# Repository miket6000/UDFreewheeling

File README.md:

# UDFreewheeling
A Freewheeling DRSSTC controller based loosely on the UD2.7. See it running my 35cm coil here: (https://youtu.be/EUlrq9CbajI)

Follow the development history at https://highvoltageforum.net/index.php?topic=2054.0

The driver behind building a new Tesla Coil Controller was to create something as simple to build and use as the UD2.7 (https://loneoceans.com/labs/ud27/) but with the below improvements:
* Freewheeling over current protection, this limits the maximum current without terminating the burst
* Over current and current phase detected with a single current transformer (CT)
* Removed the need for difficult to obtain variable inductors
* Self oscillating for improved startup at lower feedback currents

There are a couple of breaking changes that are worth pointing out:
* While the board outline is approximately the same as UD2.7 I can't guarantee the mounting holes are in the exact same locations
* There is no longer the ability to disable phase lead, it wasn't obvious why this would be required and can be done by using a short instead of L1
* The location of the HFBR is approximately the same as the UD2.7 but the location of the IF-D95 has changed slightly

Huge thanks to the assistance of all those at highvoltageforum.net and especially David Knierim for his extensive contributions.

## How it works
### Power supply
There's nothing much here to talk about, there are three regulators, 24V, 9V and 5V. 24V and 5V are linear, the 9V should be a DC/DC converter such as  RECOM Power R-78E9.0-0.5 or similar. It is recommended for the input supply that you use a 1A 24V SMPS and the DC input. Do not use the DC and AC inputs at the same time.

### Phase detect
The CT should be designed to provide a current of ~500mA to 1A peak at maximum primary current.
C32 provides HF bypass for noise. The current from the CT passes through R3 || R8 L1 and R1 generating a voltage ton pin 1 of R8 hat leads the current by theta = arctan(Xl / R). Xl depends on the operating frequency of the primary but R just depends on the position of the wiper on R8 and can be set from 5.1R up to R3 || R9 which is approximately 22R. This voltage is then clamped to +/- 0.65V by the back to back diodes and capacitvely coupled into the inverting input of the comparator IC8.

IC8 is set up with both positive and negative feedback with the non-inverting input held at nominally 2.5V. If we initially ignore any input from the CT we can see that the comparator will attempt to pull the inverting input low. There will be a time constant set by C5 and (R21 + R25) which will mean this takes some amount of time but the voltage at the input will be reducing. Meanwhile when the input transitioned low C33, R26 and R7 immediately pulled the non-inverting input low but C33 will slowly charge so the voltage at the non-inverting input will be increasing.

After some amount of time the increasing voltage on the non-inverting input and the decreasing voltage in the inverting input will be equal and the pass each other. At this moment the comparator will toggle states at the output will go high. This will reverse our initial state and everything happens again, but with the voltages reversed, i.e. it oscillates. The oscillation frequency can be set by adjusting R25. This should be set as close as possible to the frequency of the primary. To set the correct frequency ensure there is no feedback from the CT (i.e. disconnect the output stage or the CT) and measure the frequency on an oscilloscope. Adjust R25 until this matches your expected resonant frequency.

When there is a signal from the CT it swamps the ability of the negative feedback from R21 + R25 to control the inverting input pin so is effectively overriden with the natural resonant frequency of the system.

### Over current detection
The current through the CT creates a voltage across R1 (5R1). This is clamped between the 0V and 5V rails and feed into the inverting input of U5A. If the voltage exceeds the voltage set by R20 then the output of the comparator will go low signaling an over current event to the logic controlling the gate drivers. The over current threshold is determined by taking your intended over current peak, dividing it by the CT ratio and multiplying by 5.1V. R20 is then adjusted until this voltage is measured on TP6. E.G. I have a 300:1 CT and want the over current limit to be set to 200A, so I adjust R20 until I see 200A / 300 * 5.1V = 3.4V.

### Interrupt input
A signal present on the optical input of RX1 (active low) is inverted by IC4F so that the output is high when the signal is present (LED on). A signal present on the optical input of RX2 (active high) is first inverted and the pulls down the same node as RX1 which is then inverted again so that the output is again high when the signal is present. The two RX inputs are effectively OR'd together so it is not recommended to use both inputs at the same time. If RX2 is not placed it is necessary to either tie the input of IC4B low (by shorting RX2-RX1) or remove D12. Note, if you do decide to remove D12 it is still necessary to include R11 to prevent oscillation caused by a floating input to IC4B.

### Undervoltage Lockout (UVLO)
The under voltage lockout compares the 24V rail (divided by 6 and applied to the non-inverting input of U5B) to the reference voltage set by R27 applied to the inverting input of U5B. If the voltage drops below the reference voltage the output goes low signaling to the gate drive logic that an undervoltage has occured. The reference is set by dividing your desired UVLO voltage by 6 and adjusting R27 until you see the desired voltage on TP4. E.G. I want UVLO to trigger at 18V, 18V / 6 = 3V so I adjust R27 until I measure 3V on TP4.

### Gate drivers
This is borrowed directly from UD2.7C, the two UCC27423 dual inverting gate drivers are used to drive two FDD8424H complementry MOSFETs to run the gate drive transformers. The only difference is that there are seperate signals for the two GDTs. This means it is not possible to parallel the twou outputs, each needs to run its own GDT, one for each half of the full bridge. 

### Gate drive logic
This is the complex part. We'll start at the gate drivers and move backwards...
IC12 is a multiplexer. It has two sets of 4 inputs and will take one of the two sets of inputs and connect them to the outputs. The schematic uses a slightly different nomenclature than the datasheet but for each pair of input pins ('I0a' & 'I1a' are one pair) if the 'S' pin is low then the voltage at input 'I0a' is connected to output 'Za', if the 'S' pin is high then the voltage at 'I1a' is connected to 'Za'. All the pairs are switched at the same time. This is all assuming the Enable (E) pin is low, otherwise the outputs are all low.

We connect CLK to our 'S' pin. Looking at the 'a' and 'b' inputs which connect to GDT1 we can see that 'Za' and 'Zb' have complementy outputs, if 'Za' is high, 'Zb' is low and vice-verse. CLK is derived from our phase signal so always drives GDT1 in phase with the phase signal. Inputs 'c' and 'd' are more complex. They are driven by the putpus of IC6B so depending on the state of IC6B could be either driven in phase or out of phase with CLK. If they're driven in phase with CLK (i.e. 'Q' is high) then both sides of the H-bridge will be in phase with each other and there will be no voltage across the primary tank circuit, i.e. we're freewheeling. The currents in the LC circuit are free to slosh backwards and forwards without significant resistance from the bridge. If however 'Q' is low then the output to GDT2 is out of phase and the HVDC bus voltage will occure across the primary tank causing it to ring up.

IC6B samples IC6A's 'Qn' output and latches it for the next clock cycle on every rising 'CLK' edge. Under "normal" circumstances IC6A clocks in 5V on the 'D' pin so 'Qn' is 0V. 0V on the 'D' pin of IC6B means the drive is out of phase and we ring up the current. If however OCD is asserted low by the over current detect comparator at any stage during the clock cycle the output of IC6B's 'Qn' output will go high. It will stay high until the next clock edge samples the 'D' input and drives 'Qn' low again, but going low takes time, before that happens the state has already been samples by IC6B and locked in for the next cycle. The INTERRUPT signal on the 'set' pin just ensures that we're in the correct state (freewheeling off) in between on signals from the interrupter, otherwise we wouldn't be able to start.

IC5A will disable the output of IC12 whenever INTERRUPT is low and there is a rising edge on the CLK signal. It can also disable IC12 if its 'R' line is asserted low by IC5B which is used to latch the UVLO signal. This means that if the UVLO is triggered then the output will remain locked out until the next rising edge of INTERRUPT.

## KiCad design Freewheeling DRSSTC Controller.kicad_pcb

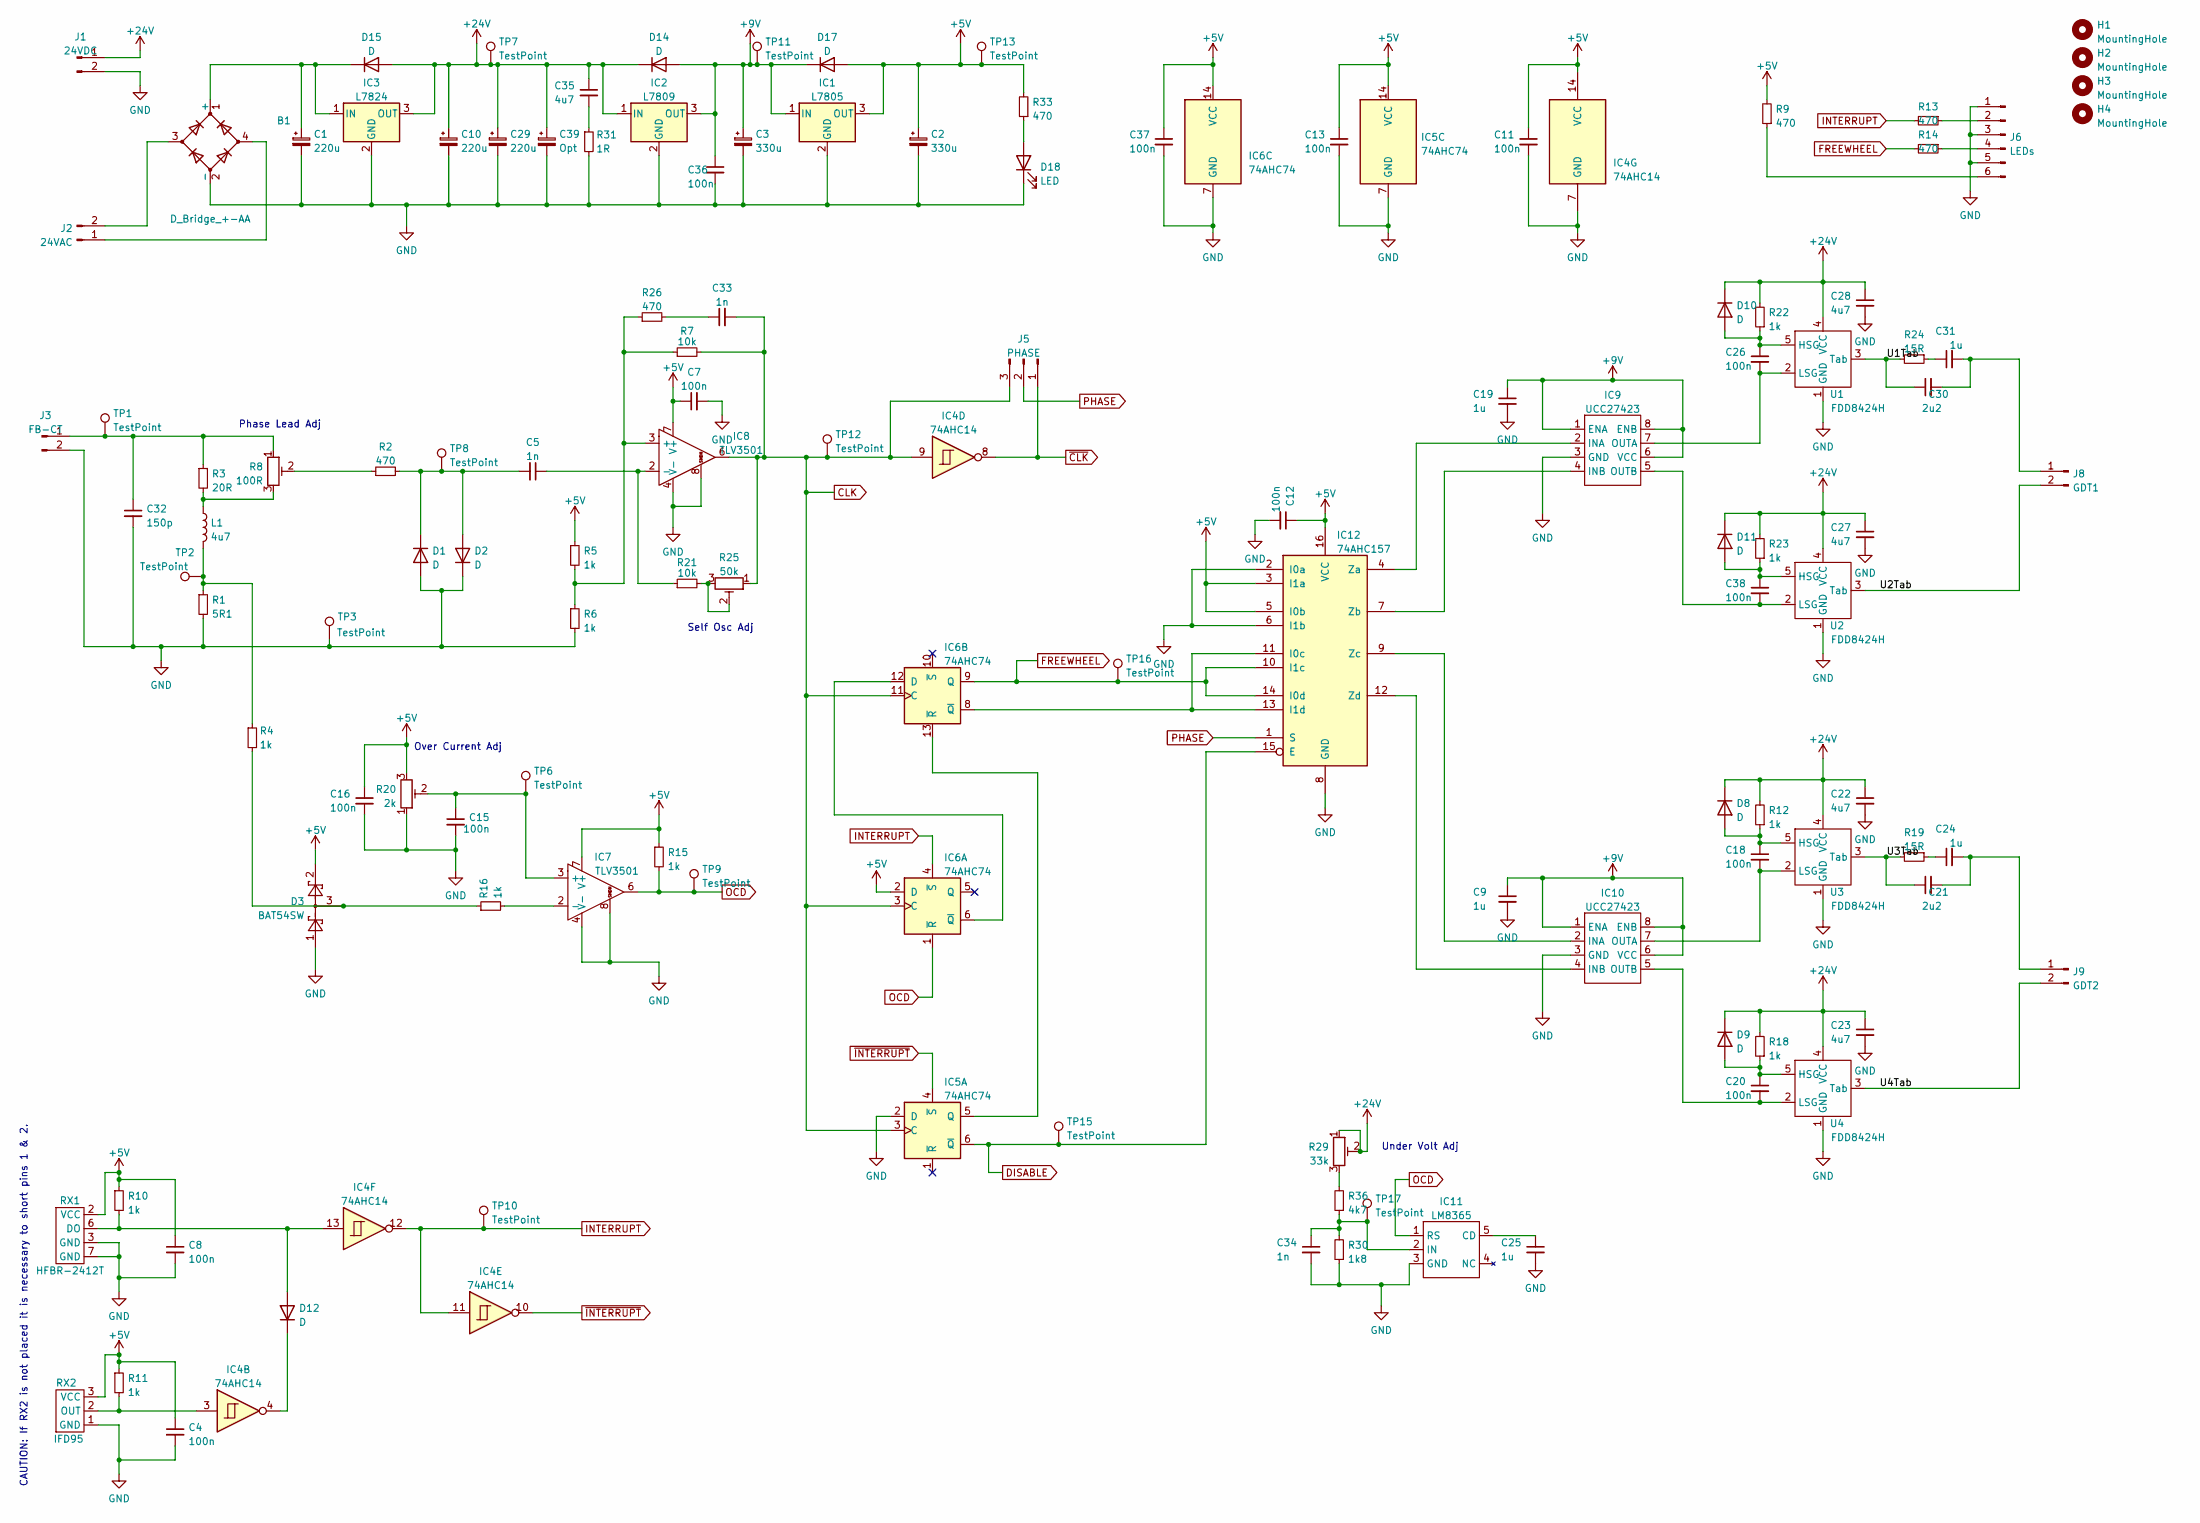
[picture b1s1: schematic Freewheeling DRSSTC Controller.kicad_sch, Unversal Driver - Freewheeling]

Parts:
B1: D_Bridge_+-AA; Diode_Bridge_Vishay_DFS
C1, C10, C29: 220u; CP_Radial_D8.0mm_P3.50mm
C2, C3: 330u; CP_Radial_D8.0mm_P3.50mm
C4, C7, C8, C11, C12, C13, C15, C16, C18, C20, C26, C36, C37, C38: 100n; C_0805_2012Metric
C5, C33, C34: 1n; C_0805_2012Metric
C9, C19, C25: 1u; C_0805_2012Metric
C21, C30: 2u2; C_1210_3225Metric
C22, C23, C27, C28, C35: 4u7; C_1206_3216Metric
C24, C31: 1u; C_1206_3216Metric
C32: 150p; C_0805_2012Metric
C39: Opt; CP_Radial_D8.0mm_P3.50mm
D1, D2, D14, D15, D17: D; D_SOD-123
D3: BAT54SW; SOT-23
D8, D9, D10, D11, D12: D; D_SOD-323
D18: LED; D_0805_2012Metric
H1, H2, H3, H4: MountingHole; MountingHole_3.2mm_M3
IC1: L7805; TO-252-3_TabPin2
IC2: L7809; TO-220-3_Vertical
IC3: L7824; TO-263-2
IC4: 74AHC14; SOIC-14_3.9x8.7mm_P1.27mm
IC5, IC6: 74AHC74; SOIC-14_3.9x8.7mm_P1.27mm
IC7, IC8: TLV3501; SOIC-8_3.9x4.9mm_P1.27mm
IC9, IC10: UCC27423; SOIC-8_3.9x4.9mm_P1.27mm
IC11: LM8365; SOT-23-5
IC12: 74AHC157; SOIC-16_3.9x9.9mm_P1.27mm
J1: 24VDC; JST_XH_B2B-XH-A_1x02_P2.50mm_Vertical
J2: 24VAC; JST_XH_B2B-XH-A_1x02_P2.50mm_Vertical
J3: FB-CT; JST_XH_B2B-XH-A_1x02_P2.50mm_Vertical
J5: PHASE; PinHeader_1x03_P2.54mm_Vertical
J6: LEDs; PinHeader_1x06_P2.54mm_Vertical
J8: GDT1; JST_XH_B2B-XH-A_1x02_P2.50mm_Vertical
J9: GDT2; JST_XH_B2B-XH-A_1x02_P2.50mm_Vertical
L1: 4u7; L_Axial_L11.0mm_D4.5mm_P5.08mm_Vertical_Fastron_MECC
R1: 5R1; R_Axial_DIN0414_L11.9mm_D4.5mm_P15.24mm_Horizontal
R2, R9, R13, R14, R26, R33: 470; R_0805_2012Metric
R3: 20R; R_Axial_DIN0414_L11.9mm_D4.5mm_P15.24mm_Horizontal
R4, R5, R6, R10, R11, R12, R15, R16, R18, R22, R23: 1k; R_0805_2012Metric
R7, R21: 10k; R_0805_2012Metric
R8: 100R; Potentiometer_Bourns_3296W_Vertical
R19, R24: 15R; R_1210_3225Metric
R20: 2k; Potentiometer_Bourns_3296W_Vertical
R25: 50k; Potentiometer_Bourns_3296W_Vertical
R29: 33k; Potentiometer_Bourns_TC33X_Vertical
R30: 1k8; R_0805_2012Metric
R31: 1R; R_0805_2012Metric
R36: 4k7; R_0805_2012Metric
RX1: HFBR-2412T; HFBR-x41x
RX2: IFD95; IF-D95
TP1, TP2, TP3, TP6, TP7, TP8, TP9, TP10, TP11, TP12, TP13, TP15, TP16, TP17: TestPoint; TestPoint_THTPad_D1.0mm_Drill0.5mm
U1, U2, U3, U4: FDD8424H; TO-252-4

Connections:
+5V: C2.1, C4.1, C7.1, C8.1, C11.1, C12.1, C13.1, C16.1, C37.1, D3.2, D17.2 (A), IC1.3 (OUT), IC4.14 (VCC), IC5.14 (VCC), IC6.2 (D), IC6.14 (VCC), IC7.7 (V+), IC8.7 (V+), IC12.3 (I1a), IC12.5 (I0b), IC12.16 (VCC), R5.1, R9.2, R10.1, R11.1, R15.1, R20.3, R33.2, RX1.2 (VCC), RX2.3 (VCC), TP13.1
+9V: C3.1, C9.1, C19.1, C36.1, D14.2 (A), D17.1 (K), IC1.1 (IN), IC2.3 (OUT), IC9.1 (ENA), IC9.6 (VCC), IC9.8 (ENB), IC10.1 (ENA), IC10.6 (VCC), IC10.8 (ENB), TP11.1
+24V: C10.1, C22.1, C23.1, C27.1, C28.1, C29.1, C35.1, C39.1, D8.1 (K), D9.1 (K), D10.1 (K), D11.1 (K), D14.1 (K), D15.2 (A), IC2.1 (IN), IC3.3 (OUT), J1.1, R12.2, R18.2, R22.2, R23.2, R29.1, R29.2, TP7.1, U1.4 (VCC), U2.4 (VCC), U3.4 (VCC), U4.4 (VCC)
/U1Tab: C30.1, R24.2, U1.3 (Tab)
/U2Tab: J8.2, U2.3 (Tab)
/U3Tab: C21.1, R19.2, U3.3 (Tab)
/U4Tab: J9.2, U4.3 (Tab)
CLK: C33.2, IC4.9, IC5.3 (C), IC6.3 (C), IC6.11 (C), IC8.6, J5.3, R7.2, R25.1, TP12.1
DISABLE: IC5.6 (~Q), IC12.15 (E), TP15.1
FREEWHEEL: IC6.9 (Q), IC12.10 (I1c), IC12.14 (I0d), R14.2, TP16.1
GND: B1.2 (-), C1.2, C2.2, C3.2, C4.2, C7.2, C8.2, C9.2, C10.2, C11.2, C12.2, C13.2, C15.2, C16.2, C19.2, C22.2, C23.2, C25.2, C27.2, C28.2, C29.2, C32.2, C34.2, C36.2, C37.2, C39.2, D1.2 (A), D2.1 (K), D3.1, D18.1 (K), IC1.2 (GND), IC2.2 (GND), IC3.2 (GND), IC4.7 (GND), IC5.2 (D), IC5.7 (GND), IC6.7 (GND), IC7.4 (V-), IC7.8, IC8.4 (V-), IC8.8, IC9.3 (GND), IC10.3 (GND), IC11.3 (GND), IC12.2 (I0a), IC12.6 (I1b), IC12.8 (GND), J1.2, J3.2, J6.1, J6.3, J6.5, R1.2, R6.2, R20.1, R30.1, R31.2, RX1.3 (GND), RX1.7 (GND), RX2.1 (GND), TP3.1, U1.1 (GND), U2.1 (GND), U3.1 (GND), U4.1 (GND)
INTERRUPT: IC4.11, IC4.12, IC6.4 (~S), R13.2, TP10.1
unnamed: B1.1 (+), C1.1, D15.1 (K), IC3.1 (IN)
unnamed: B1.3, J2.2
unnamed: B1.4, J2.1
unnamed: C18.1, D8.2 (A), R12.1, U3.5 (HSG)
unnamed: C18.2, IC10.7 (OUTA), U3.2 (LSG)
unnamed: C20.1, D9.2 (A), R18.1, U4.5 (HSG)
unnamed: C20.2, IC10.5 (OUTB), U4.2 (LSG)
unnamed: C21.2, C24.2, J9.1
unnamed: C24.1, R19.1
unnamed: C25.1, IC11.5 (CD)
unnamed: C26.1, D10.2 (A), R22.1, U1.5 (HSG)
unnamed: C26.2, IC9.7 (OUTA), U1.2 (LSG)
unnamed: C30.2, C31.2, J8.1
unnamed: C31.1, R24.1
unnamed: C33.1, R26.2
unnamed: C34.1, IC11.2 (IN), R30.2, R36.1, TP17.1
unnamed: C35.2, R31.1
unnamed: C38.1, D11.2 (A), R23.1, U2.5 (HSG)
unnamed: C38.2, IC9.5 (OUTB), U2.2 (LSG)
unnamed: C5.2, D1.1 (K), D2.2 (A), R2.2, TP8.1
unnamed: D12.1 (K), IC4.4
unnamed: D12.2 (A), IC4.13, R10.2, RX1.6 (DO)
unnamed: D18.2 (A), R33.1
unnamed: IC4.3, R11.2, RX2.2 (OUT)
unnamed: IC6.8 (~Q), IC12.11 (I0c), IC12.13 (I1d)
unnamed: IC6.6 (~Q), IC6.12 (D)
unnamed: IC5.5 (Q), IC6.13 (~R)
unnamed: IC7.2 (-), R16.2
unnamed: C5.1, IC8.2 (-), R21.1
unnamed: IC9.2 (INA), IC12.4 (Za)
unnamed: IC9.4 (INB), IC12.7 (Zb)
unnamed: IC10.2 (INA), IC12.9 (Zc)
unnamed: IC10.4 (INB), IC12.12 (Zd)
unnamed: J6.2, R13.1
unnamed: J6.4, R14.1
unnamed: J6.6, R9.1
unnamed: L1.1, R3.2, R8.3
unnamed: L1.2, R1.1, R4.1, TP2.1
unnamed: C32.1, J3.1, R3.1, R8.1, TP1.1
unnamed: R2.1, R8.2
unnamed: D3.3, R4.2, R16.1
unnamed: C15.1, IC7.3 (+), R20.2, TP6.1
unnamed: R21.2, R25.2, R25.3
unnamed: IC8.3 (+), R5.2, R6.1, R7.1, R26.1
unnamed: R29.3, R36.2
OCD: IC6.1 (~R), IC7.6, IC11.1 (RS), R15.2, TP9.1
PHASE: IC12.1 (S), J5.2
~CLK: IC4.8, J5.1
~INTERRUPT: IC4.10, IC5.4 (~S)

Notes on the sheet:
CAUTION: If RX2 is not placed it is necessary to short pins 1 & 2.
Over Current Adj
Under Volt Adj
Self Osc Adj
Phase Lead Adj

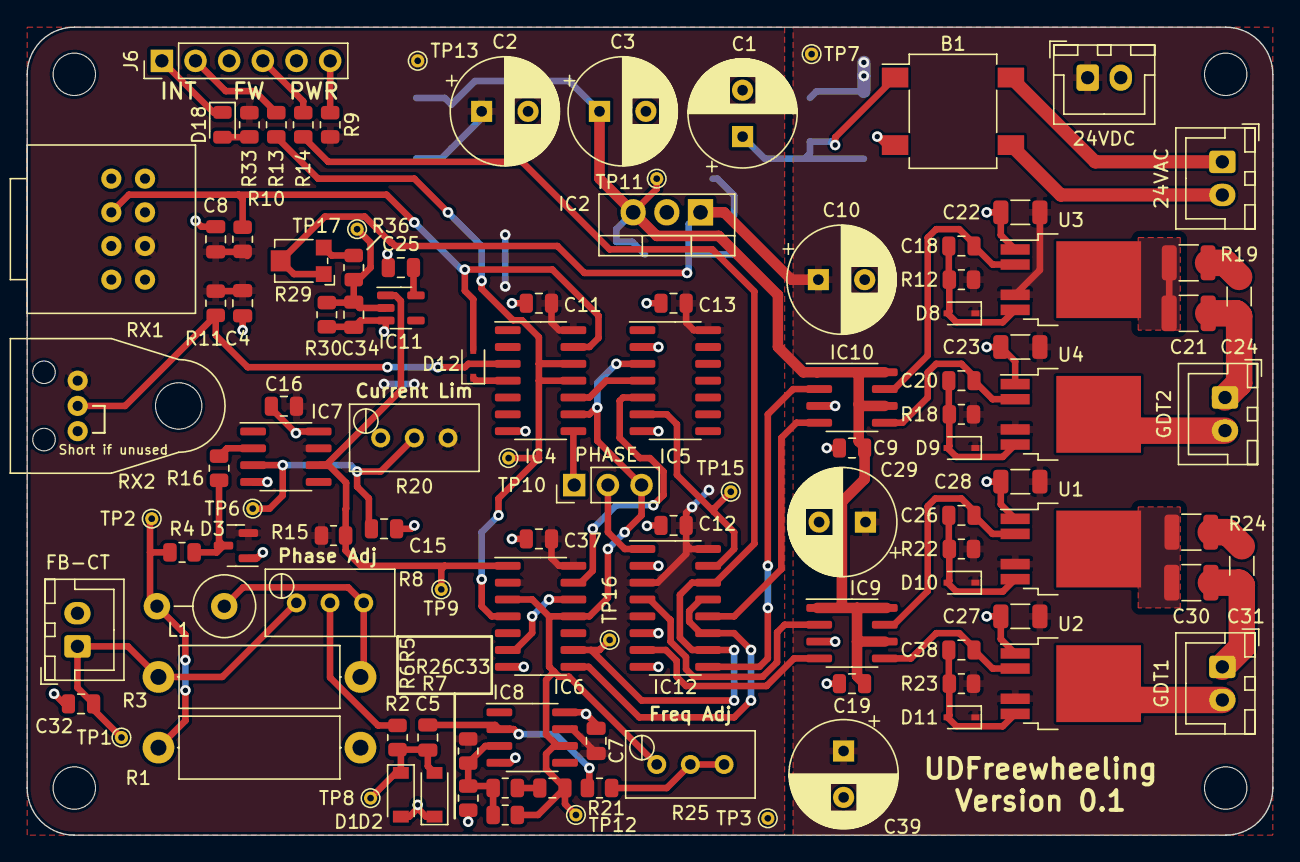
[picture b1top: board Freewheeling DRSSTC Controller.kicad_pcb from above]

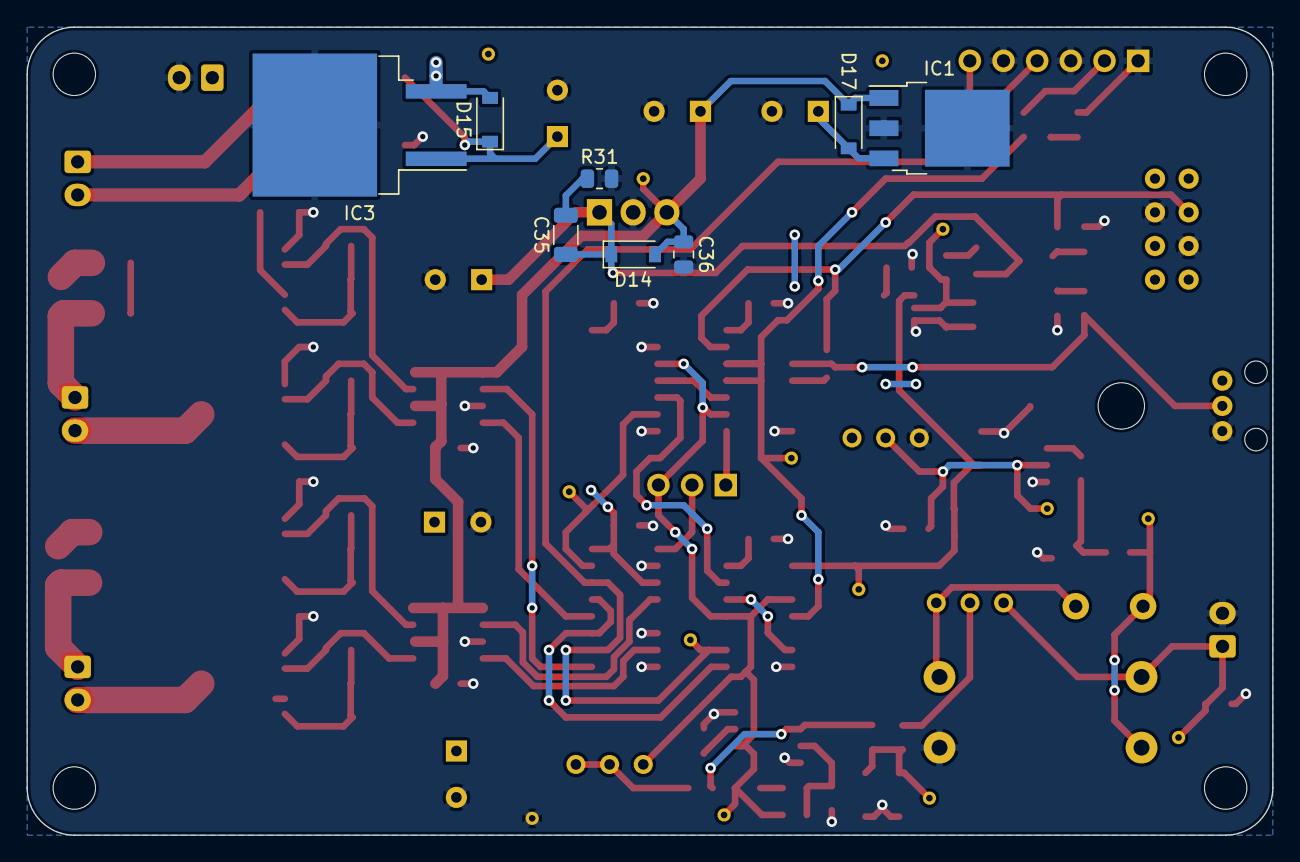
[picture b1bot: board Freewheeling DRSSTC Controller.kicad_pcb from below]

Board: 2 copper layers, 94.0 x 61.0 mm, 123 parts (8 on the bottom side), 61 nets.

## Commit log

2022-07-17 Create README.md
    Initial Readme
2022-07-17 Initial commit of design files
2022-07-17 Delete fp-info-cache
    Unnecessary file as it's automatically regenerated from the project files
2025-05-13 Update README.md
    Added link to youtube video of coil being driven by the UDFreewheeling
